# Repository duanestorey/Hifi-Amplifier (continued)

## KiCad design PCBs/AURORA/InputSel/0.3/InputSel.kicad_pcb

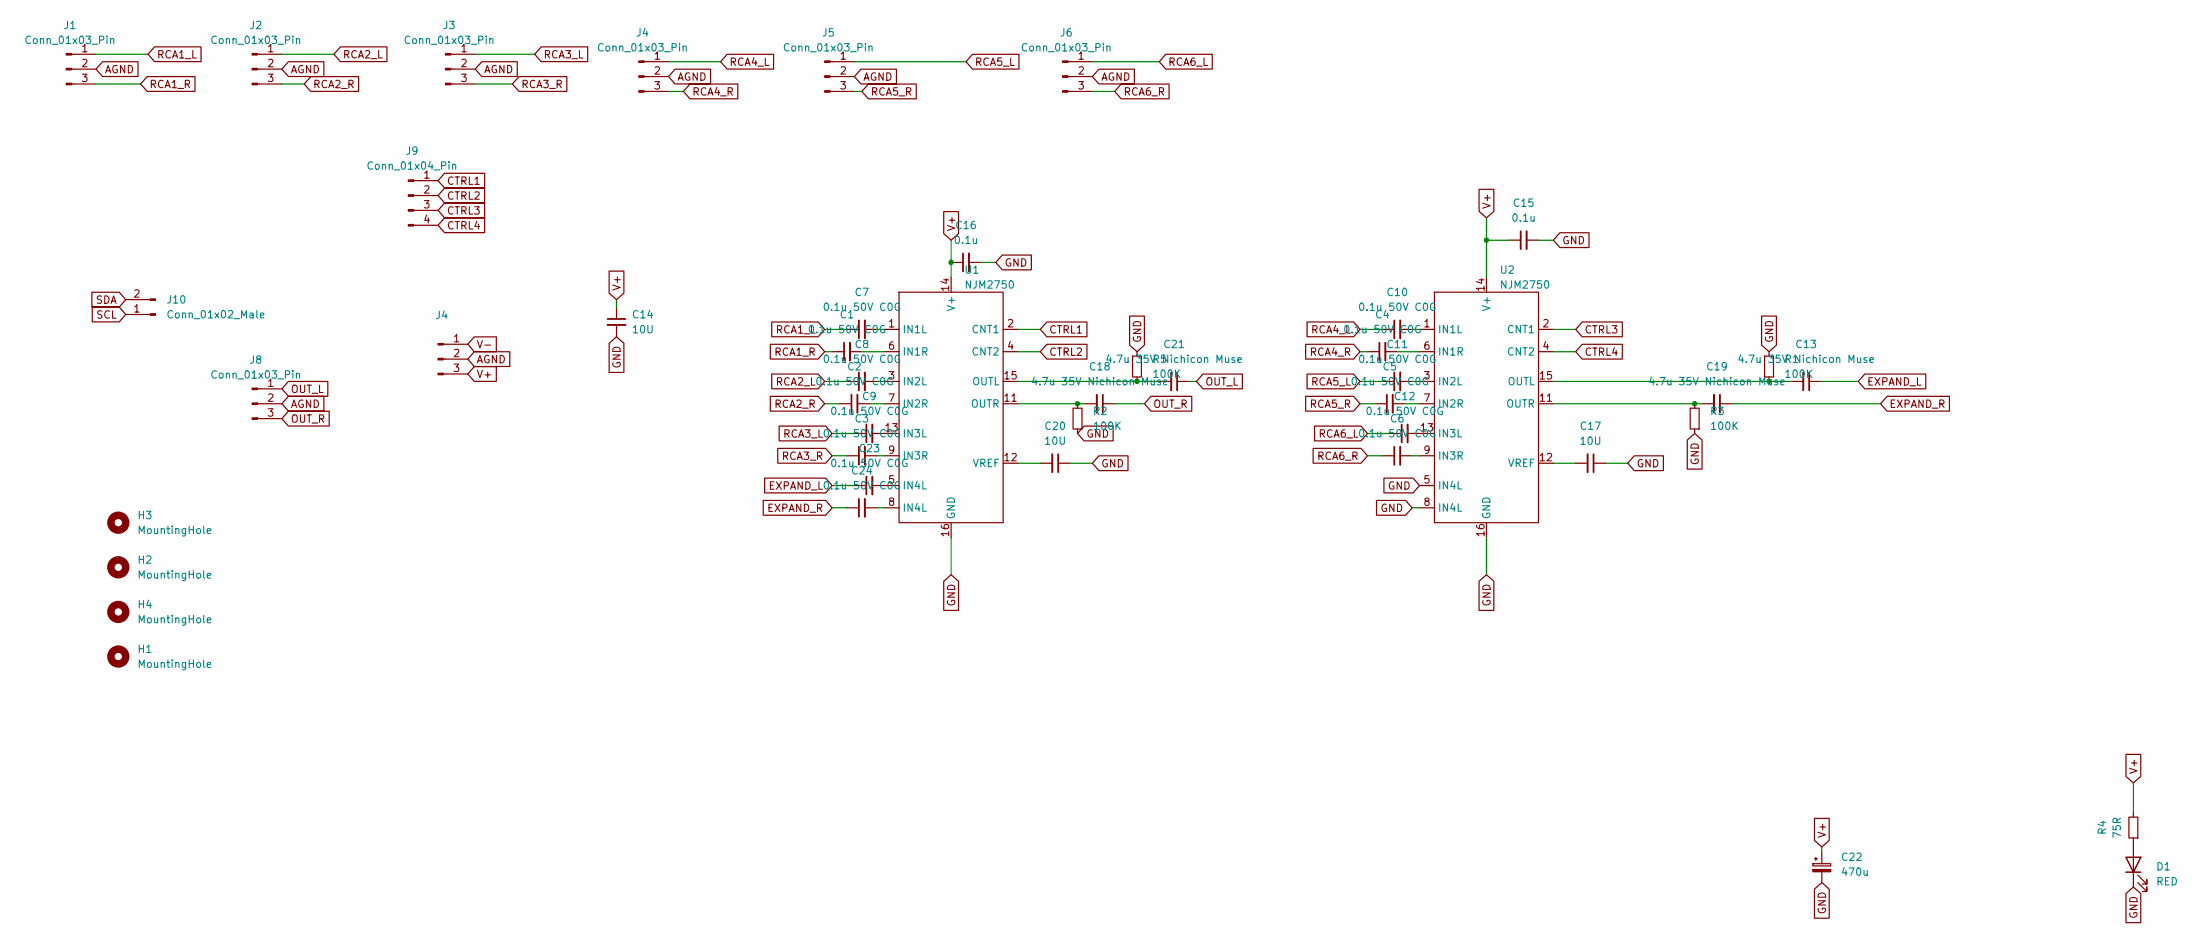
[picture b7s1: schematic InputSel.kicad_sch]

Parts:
C1, C2, C3, C4, C5, C6, C7, C8, C9, C10, C11, C12, C23, C24: 0.1u 50V C0G; C_1206_3216Metric_Pad1.33x1.80mm_HandSolder; Mouser 81-GRM3195C1H104JA5D
C13, C18, C19, C21: 4.7u 35V Nichicon Muse; CP_Radial_D5.0mm_P2.00mm
C14, C17, C20: 10U; C_1206_3216Metric_Pad1.33x1.80mm_HandSolder
C15, C16: 0.1u; C_0805_2012Metric_Pad1.18x1.45mm_HandSolder
C22: 470u; CP_Radial_D6.3mm_P2.50mm
D1: RED; LED_0805_2012Metric
H1, H2, H3, H4: MountingHole; MountingHole_3.2mm_M3_DIN965_Pad_TopOnly
J1, J2, J3, J5, J6, J8: Conn_01x03_Pin; JST_PH_B3B-PH-K_1x03_P2.00mm_Vertical
J4: Conn_01x03_Male; JST_PH_B3B-PH-K_1x03_P2.00mm_Vertical
J9: Conn_01x04_Pin; JST_PH_B4B-PH-K_1x04_P2.00mm_Vertical
J10: Conn_01x02_Male; JST_PH_B2B-PH-K_1x02_P2.00mm_Vertical
R1, R2, R3, R5: 100K; R_0603_1608Metric_Pad0.98x0.95mm_HandSolder; Mouser 603-AT0603FRE07100KL
R4: 75R; R_0603_1608Metric_Pad0.98x0.95mm_HandSolder
U1, U2: NJM2750; SOP-16_4.4x10.4mm_P1.27mm; Mouser NJM2750M

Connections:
AGND: J1.2, J2.2, J3.2, J4.2, J5.2, J6.2, J8.2; also elsewhere on the board
CTRL1: J9.1, U1.2 (CNT1)
CTRL2: J9.2, U1.4 (CNT2)
CTRL3: J9.3, U2.2 (CNT1)
CTRL4: J9.4, U2.4 (CNT2)
EXPAND_L: C13.1, C23.1
EXPAND_R: C19.1, C24.1
GND: C14.2, C15.2, C16.2, C17.1, C20.1, C22.2, D1.1 (K), R1.1, R2.1, R3.1, R5.1, U1.16 (GND), U2.5 (IN4L), U2.8 (IN4L), U2.16 (GND)
unnamed: C23.2, U1.5 (IN4L)
unnamed: C24.2, U1.8 (IN4L)
unnamed: D1.2 (A), R4.1
unnamed: C7.2, U1.1 (IN1L)
unnamed: C1.2, U1.6 (IN1R)
unnamed: C8.2, U1.3 (IN2L)
unnamed: C2.2, U1.7 (IN2R)
unnamed: C9.2, U1.13 (IN3L)
unnamed: C3.2, U1.9 (IN3R)
unnamed: C21.2, R5.2, U1.15 (OUTL)
unnamed: C18.2, R2.2, U1.11 (OUTR)
unnamed: C20.2, U1.12 (VREF)
unnamed: C10.2, U2.1 (IN1L)
unnamed: C4.2, U2.6 (IN1R)
unnamed: C11.2, U2.3 (IN2L)
unnamed: C5.2, U2.7 (IN2R)
unnamed: C12.2, U2.13 (IN3L)
unnamed: C6.2, U2.9 (IN3R)
unnamed: C13.2, R1.2, U2.15 (OUTL)
unnamed: C19.2, R3.2, U2.11 (OUTR)
unnamed: C17.2, U2.12 (VREF)
OUT_L: C21.1, J8.1
OUT_R: C18.1, J8.3
RCA1_L: C7.1, J1.1
RCA1_R: C1.1, J1.3
RCA2_L: C8.1, J2.1
RCA2_R: C2.1, J2.3
RCA3_L: C9.1, J3.1
RCA3_R: C3.1, J3.3
RCA5_L: C11.1, J5.1
RCA5_R: C5.1, J5.3
RCA6_L: C12.1, J6.1
RCA6_R: C6.1, J6.3
SCL: J10.1
SDA: J10.2

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
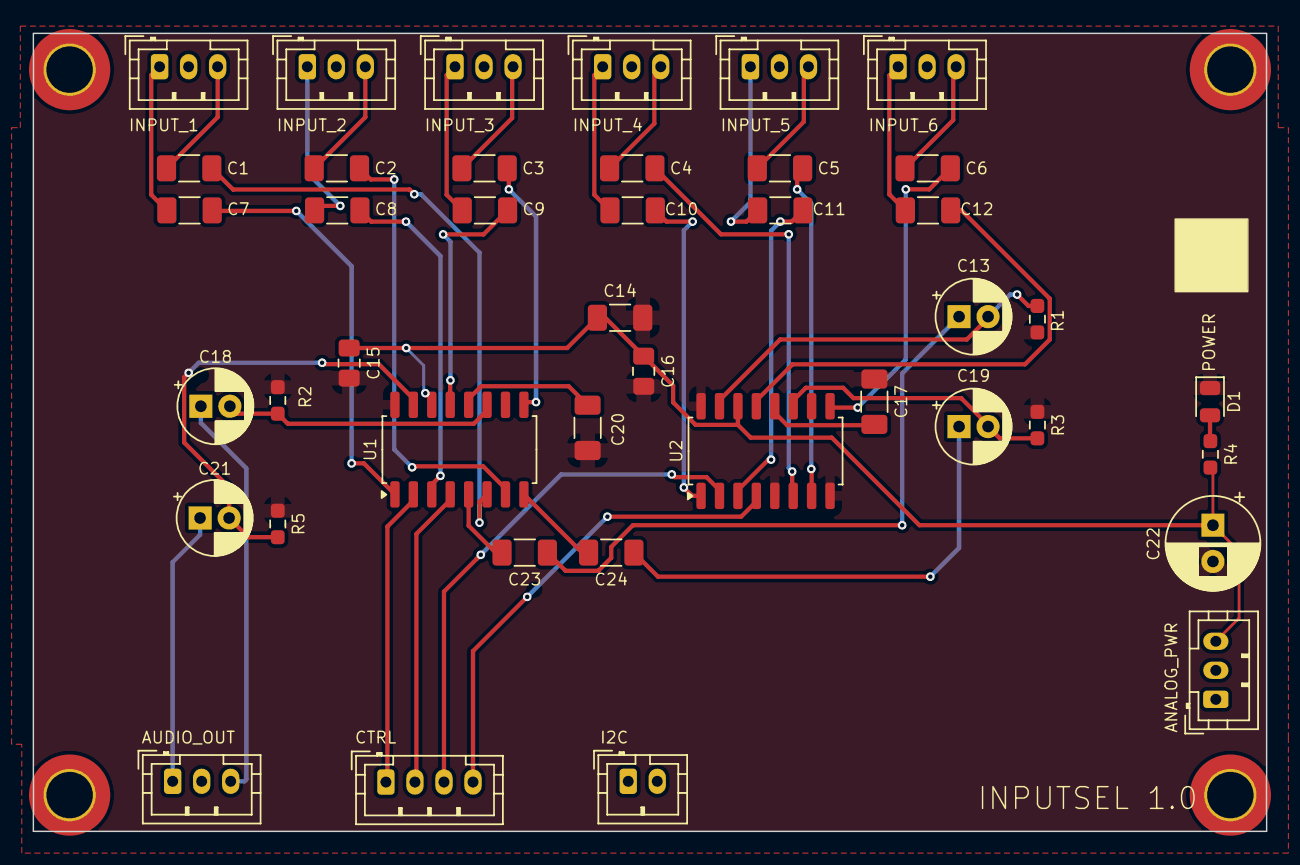
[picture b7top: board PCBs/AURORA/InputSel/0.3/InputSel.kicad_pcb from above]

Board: 2 copper layers, 85.0 x 55.0 mm, 46 parts (0 on the bottom side), 44 nets.

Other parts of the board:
J7: Conn_01x03_Male; JST_PH_B3B-PH-K_1x03_P2.00mm_Vertical

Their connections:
AGND: J7.2; also elsewhere on the board
